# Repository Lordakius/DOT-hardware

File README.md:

# DOT-hardware

## IMPORTANT

work continues on JunITer team page: https://github.com/CCT-JunITer/DoSiTracking-HW

## Requirements

* (todo): boards and used chips (ESP8266)
* some way of flashing code to the board (e.g. Arduino IDE) 
  
## Installation

* Either use the library directory in the repo or copy the files to your
  Arduino/libraries/ folder 
* configure your setup for your board:
  
  - Add http://arduino.esp8266.com/stable/package_esp8266com_index.json to your
    Additional Boards Manager URL
  - Download the ESP8266 boards
  - choose board 'WeMos D1 R1' 
  - set up the correct port

## ToDo

* finish readme
* implement connection with backend

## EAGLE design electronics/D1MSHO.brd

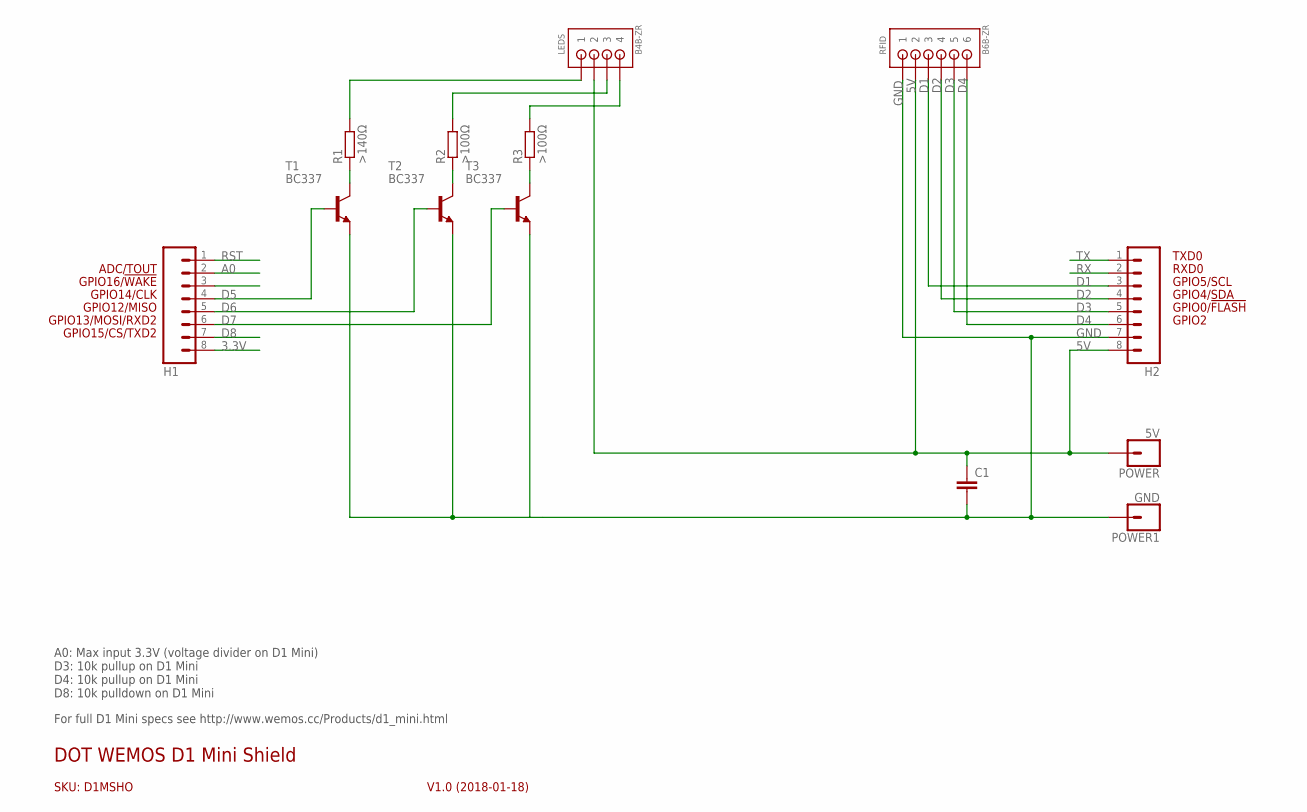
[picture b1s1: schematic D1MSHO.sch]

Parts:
C1: C-EU050-025X075; C050-025X075
H1, H2: M08; 1X08
LEDS: B4B-ZR
POWER: 5V; 1X01_OFFSET
POWER1: GND; 1X01_OFFSET
R1: >140Ω; 0204/5
R2, R3: >100Ω; 0204/5
RFID: B6B-ZR
T1, T2, T3: BC337; TO92

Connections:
3.3V: H1.8
5V: C1.1, H2.8, LEDS.2, POWER.1, RFID.2
A0: H1.2
D1: H2.3, RFID.3
D2: H2.4, RFID.4
D3: H2.5, RFID.5
D4: H2.6, RFID.6
D5: H1.4, T1.2 (B)
D6: H1.5, T2.2 (B)
D7: H1.6, T3.2 (B)
D8: H1.7
GND: C1.2, H2.7, POWER1.1, RFID.1, T1.1 (E), T2.1 (E), T3.1 (E)
unnamed: R1.1, T1.3 (C)
unnamed: LEDS.1, R1.2
unnamed: LEDS.3, R2.2
unnamed: LEDS.4, R3.2
unnamed: R2.1, T2.3 (C)
unnamed: R3.1, T3.3 (C)
RST: H1.1
RX: H2.2
TX: H2.1

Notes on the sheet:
GPIO2
GPIO0/!FLASH
GPIO12/MISO
GPIO4/SDA
GPIO5/SCL
RXD0
TXD0
GPIO13/MOSI/RXD2
GPIO14/CLK
GPIO15/CS/TXD2
GPIO16/!WAKE
SKU: D1MSHO
DOT WEMOS D1 Mini Shield
V1.0 (2018-01-18)
ADC/TOUT
A0: Max input 3.3V (voltage divider on D1 Mini) D3: 10k pullup on D1 Mini D4: 10k pullup on D1 Mini D8: 10k pulldown on D1 Mini
For full D1 Mini specs see http://www.wemos.cc/Products/d1_mini.html

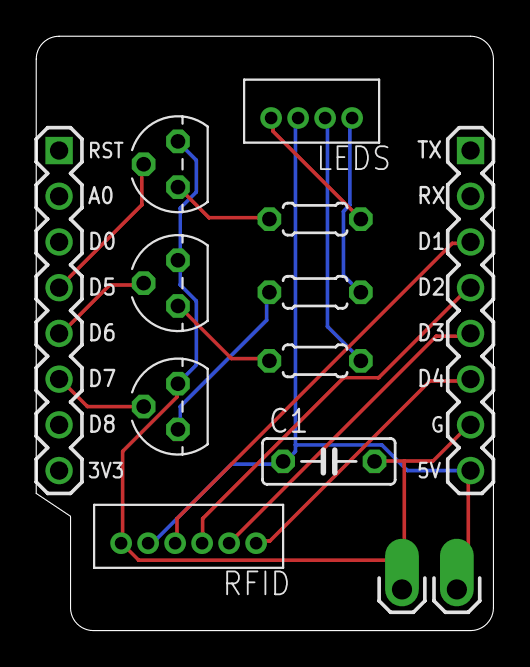
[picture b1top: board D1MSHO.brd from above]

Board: 2 copper layers, 25.4 x 33.0 mm, 13 parts (0 on the bottom side), 15 nets.

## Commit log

2018-12-10 Transferred inital structure
2018-12-10 Added multi-stage build
2018-12-10 Added Pin library
2018-12-26 Added new PN532 library
2018-12-26 Add new requirements
2018-12-26 switched to i2c
2018-12-26 final push - switch to arduino based system
2019-02-19 Rebuilt the whole hardware based on an ESP8266
2019-11-20 DOT prototype code
2020-02-05 Added new tracker
2020-02-16 removed all functions that are not needed for RFID reading
2020-02-16 modified light to signal if a card is currently read
2020-02-16 started readme
2020-02-16 added installation instructions to readme
2020-02-20 made layout accessible with KiCAD

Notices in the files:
parts and their libraries:
freetronics-original: Licensing: CC v3.0 Share-Alike You are welcome to use this library for commercial purposes.
SparkFun-Connectors: Licensing: Creative Commons ShareAlike 4.0 International - https://creativecommons.org/licenses/by-sa/4.0
